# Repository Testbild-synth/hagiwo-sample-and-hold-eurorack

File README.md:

# HAGIWO 47 - Sample and Hold Eurorack Module

This is a 4HP eurorack PCB for the HAGIWO sample and hold.
For more info on the module, see:
https://www.youtube.com/watch?v=DoiZ9PZacQo

## Status: Confirmed working!

## Hardware / PCBs
The gerbers folder contains files for one panel pcb and one circuit pcb. 
Build is fairly easy and straightforward, just order with standard settings from
jlcpcb.com or another pcb service of your choice.

BOM can be found as a csv file in the repo.

Build is fairly straight forward, not much to say here.

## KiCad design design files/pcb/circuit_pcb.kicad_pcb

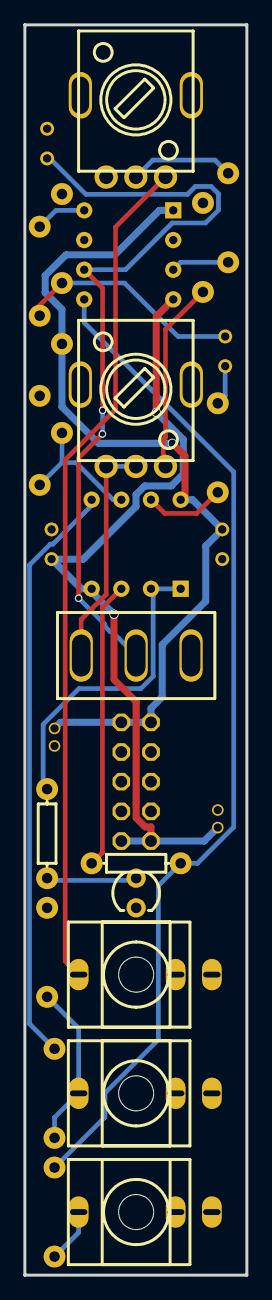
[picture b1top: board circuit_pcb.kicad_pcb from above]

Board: 2 copper layers, 19.0 x 107.0 mm, 28 parts (0 on the bottom side), 21 nets.

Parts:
C1, C2: 10u; CAP-D4.0×F1.5
C3: 1nf; RAD-0.1
C4: 2.2uf; RAD-0.1
C5, C6: 100nf; RAD-0.1
D1: 1n4148; DIODE-1N4148
EP1: PWER; EURORACK_POWER_V2
J1: IN; THONKICONN_1
J2: TRIG; THONKICONN_1
J3: OUT; THONKICONN_1
LED1: LED TBR; LED-3MM/2.54
LEVEL: 100k; R09-5KΩ
R1, R2, R4, R5, R11: 10k; R_AXIAL-0.3
R3: 33k; R_AXIAL-0.3
R6, R7: 100k; R_AXIAL-0.3
R8, R9, R10: 1k; R_AXIAL-0.3
REL: 100k; R09-5KΩ
S1: REL; TOGGLE SWITCH SPDT RED 3 PIN ON-OFF-ON 3 SPDT SMALL AC 6A/1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
U1: TL072; DIP8
U3: LF398; DIP8

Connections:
12V: C2.1, C6.1, EP1.12, R3.1, U1.8, U3.1
-12V: C1.2, C5.2, EP1.-12, U1.4, U3.4
C3_1: C3.1, R5.1
C3_2: C3.2, D1.A, R7.1
C4_2: C4.2, S1.2, U3.6
D1_C: D1.C, U3.8
GND: C1.1, C2.2, C4.1, C5.1, C6.2, EP1.GND0, EP1.GND1, EP1.GND2, EP1.GND3, EP1.GND4, EP1.GND5, J1.1, J1.2, J2.1, J2.2, J3.1, LED1.2, LEVEL.1, R4.2, R6.1, R7.2, R8.2, U3.7
J1_3: J1.3, LEVEL.3
J2_3: J2.3, R2.2, R6.2
LEVEL_2: LEVEL.2, R1.2
R1_1: R1.1, U3.3
R9_1: J3.3, R9.1
R9_2: R9.2, R10.2, U3.5
R11_1: LED1.1, R11.1
REL_3: R8.1, REL.3
S1_3: REL.1, REL.2, S1.3
U1_1: R11.2, U1.1, U1.2
U1_3: R10.1, U1.3
U1_5: R2.1, U1.5
U1_6: R3.2, R4.1, U1.6
U1_7: R5.2, U1.7

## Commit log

2024-12-11 initial file upload
